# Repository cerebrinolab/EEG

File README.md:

# EEG para analise e neuro-feedback usando Arduino e circuitos DIY.

## Captura

Essa é a tela de captura, inicialmente com uma interface minimalista, com diferentes gráficos combinados para facilitar a leitura.

Primeiro gráfico - sinal x tempo:
Aqui é possível acompanhar o sinal capturado, o eixo horizontal esta graduado em mili segundos.

Segundo grafico - espectrograma:
Plota o espectro de frequancia, num intervado de 0 á 80Hz

Terceiro grafico - Grafico de barras
Semelhante ao grafico de espectro, permite visualisar de forma simples e direta, as faixas de ondas:
Delta (0 a 4 Hz)
Theta (4 a 8 Hz)
Alpha (8 a 13 Hz)
Beta (13 a 30 Hz)
Gama (30 a 80 Hz)

## Análise por Inteligência Artificial

O sinal do gráfico abaixo foi processado por I.A., treinada com datasets etiquetados para olhos abertos, fechados, piscadas e movimentos musculares.
Esse sinal com duração de 6 minutos, alternando minuto a minuto entre olhos abertos e olhos fechados, iniciando com os olhos abertos.
Atualmente a análise é feita offline, mas o objetivo é que a I.A. efetue a análise em tempo real e que a interface traduza o resultado em estímulos sonoros e visuais, possibilitando que o usuário possa aprender a controlar seus estados mentais.

## Placa
Circuito de aquisição de sinais

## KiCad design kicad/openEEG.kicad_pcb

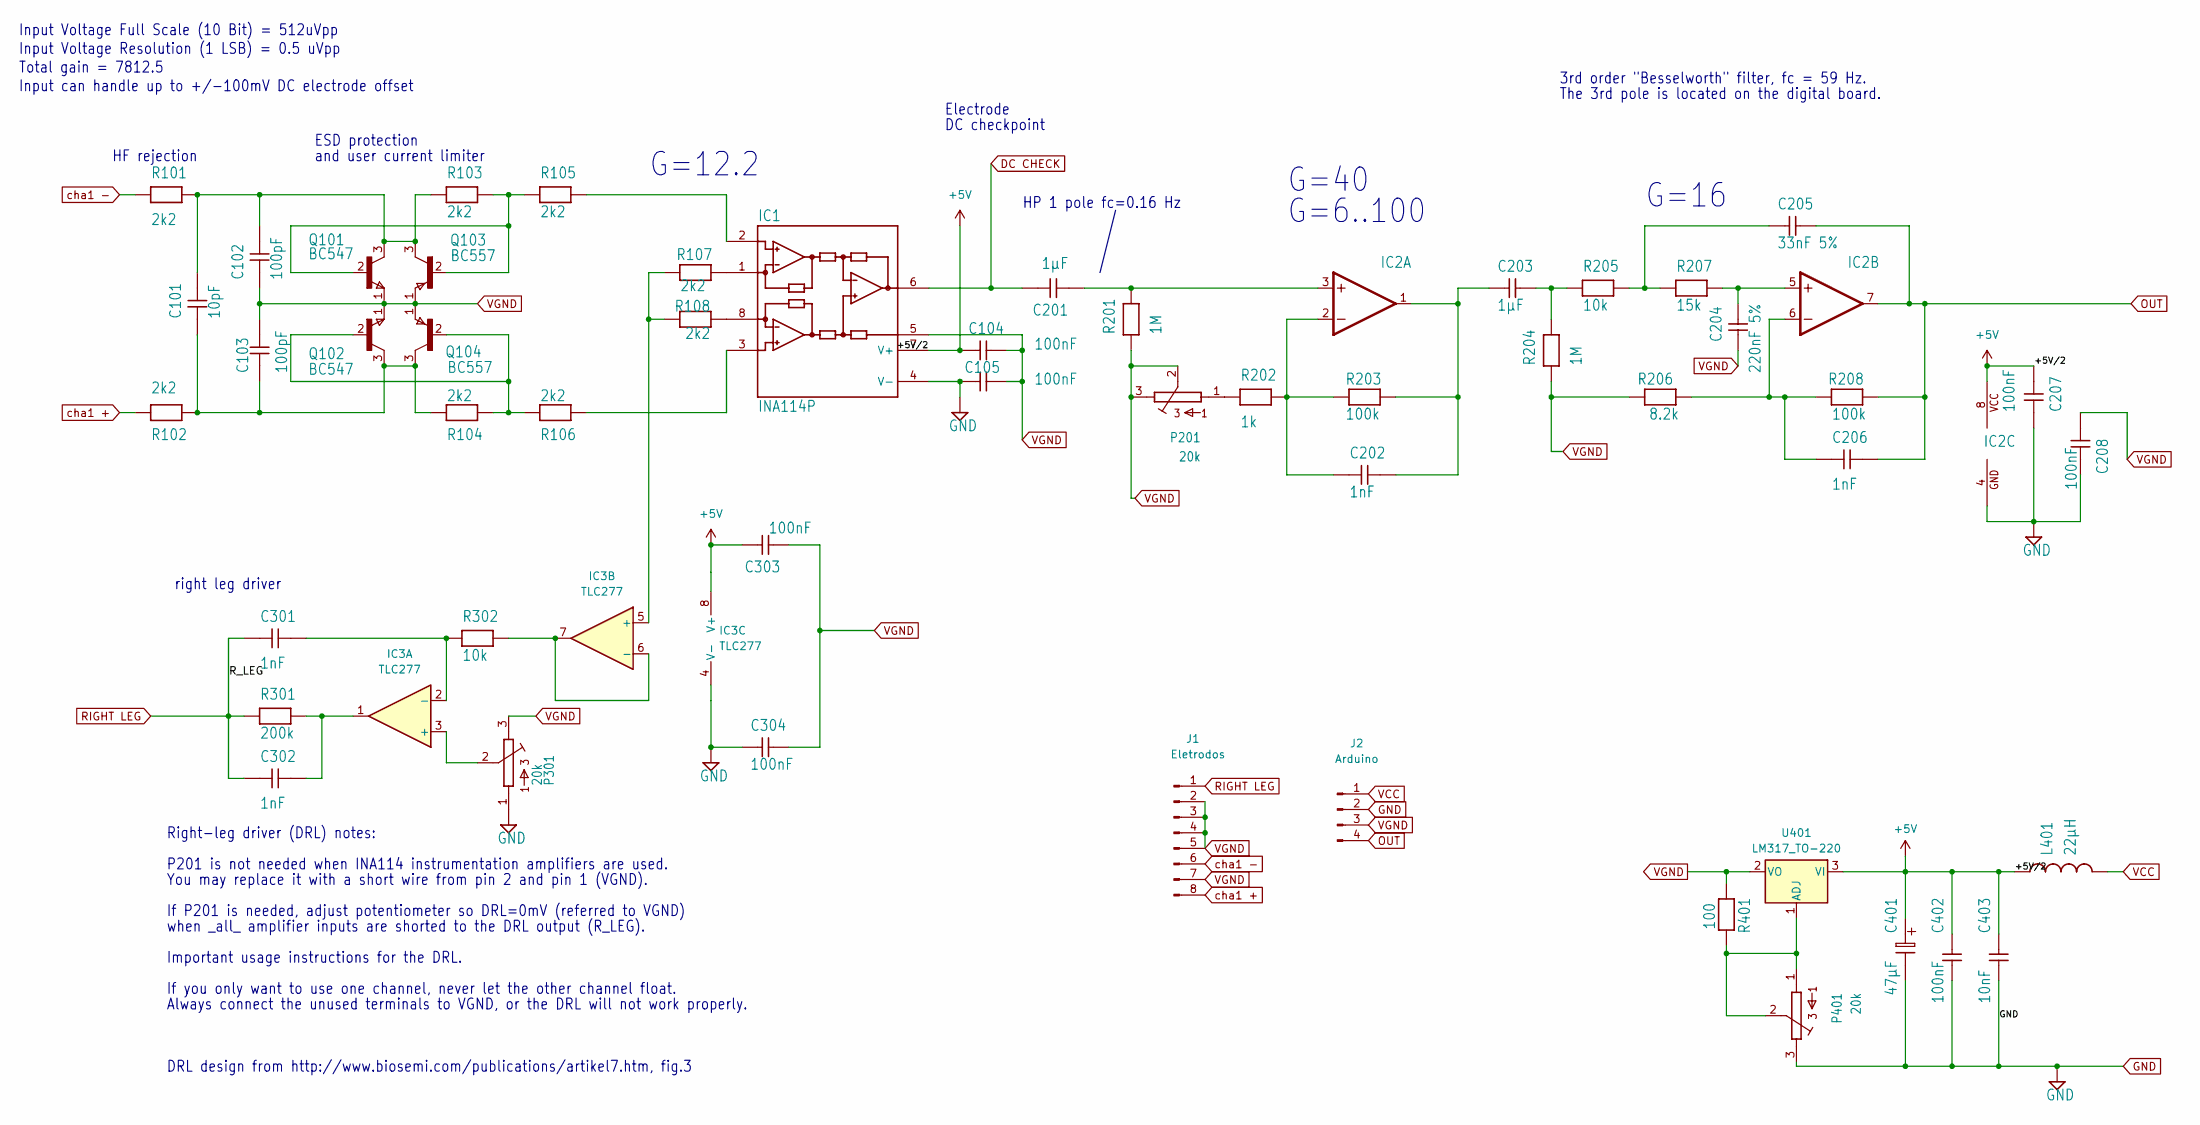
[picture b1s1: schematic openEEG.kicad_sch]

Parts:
C101: 10pF; R_Axial_DIN0204_L3.6mm_D1.6mm_P2.54mm_Vertical
C102, C103: 100pF; R_Axial_DIN0204_L3.6mm_D1.6mm_P2.54mm_Vertical
C104, C105, C207, C208, C303, C304, C402: 100nF; R_Axial_DIN0204_L3.6mm_D1.6mm_P2.54mm_Vertical
C201, C203: 1µF; CP_Radial_Tantal_D4.5mm_P2.50mm
C202, C206, C301, C302: 1nF; R_Axial_DIN0204_L3.6mm_D1.6mm_P2.54mm_Vertical
C204: 220nF 5%; R_Axial_DIN0204_L3.6mm_D1.6mm_P2.54mm_Vertical
C205: 33nF 5%; R_Axial_DIN0204_L3.6mm_D1.6mm_P2.54mm_Vertical
C401: 47µF; CP_Radial_D5.0mm_P2.50mm
C403: 10nF; R_Axial_DIN0204_L3.6mm_D1.6mm_P2.54mm_Vertical
IC1: INA114P; DIL-08
IC2: TLC277P; DIL-08
IC3: TLC277; DIL-08
J1: Eletrodos; PinHeader_2x04_P2.54mm_Vertical
J2: Arduino; PinHeader_1x04_P2.54mm_Vertical
L401: 22µH; L_Radial_L7.5mm_W4.6mm_P5.00mm_Neosid_SD75
P201, P301, P401: 20k; Potentiometer_Bourns_3386P_Vertical
Q101, Q102: BC547; TO92alinhado
Q103, Q104: BC557; TO92alinhado
R101, R102, R103, R104, R107, R108: 2k2; R_Axial_DIN0204_L3.6mm_D1.6mm_P2.54mm_Vertical
R105, R106: 2k2; R_Axial_DIN0204_L3.6mm_D1.6mm_P5.08mm_Vertical
R201, R204: 1M; R_Axial_DIN0204_L3.6mm_D1.6mm_P2.54mm_Vertical
R202: 1k; R_Axial_DIN0204_L3.6mm_D1.6mm_P2.54mm_Vertical
R203, R208: 100k; R_Axial_DIN0204_L3.6mm_D1.6mm_P2.54mm_Vertical
R205: 10k; R_Axial_DIN0204_L3.6mm_D1.6mm_P2.54mm_Vertical
R206: 8.2k; R_Axial_DIN0204_L3.6mm_D1.6mm_P2.54mm_Vertical
R207: 15k; R_Axial_DIN0204_L3.6mm_D1.6mm_P2.54mm_Vertical
R301: 200k; R_Axial_DIN0204_L3.6mm_D1.6mm_P2.54mm_Vertical
R302: 10k; R_Axial_DIN0204_L3.6mm_D1.6mm_P7.62mm_Horizontal
R401: 100; R_Axial_DIN0204_L3.6mm_D1.6mm_P2.54mm_Vertical
U401: LM317_TO-220; TO-220-3_Vertical

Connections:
+5V: C104.1, C207.2, C303.2, C401.1, C402.2, C403.2, IC1.7 (V+), IC2.8 (VCC), IC3.8 (V+), L401.1, U401.3 (VI)
DC CHECK: C201.2, IC1.6 (OUT)
GND: C105.1, C207.1, C208.1, C304.1, C401.2, C402.1, C403.1, IC1.4 (V-), IC2.4 (GND), IC3.4 (V-), J2.2, P301.1, P401.3
unnamed: C203.2, R204.2, R205.1
unnamed: C205.1, R205.2, R207.1
unnamed: C302.2, IC3.1, R301.2
unnamed: IC1.3 (+IN), R106.2
unnamed: IC1.2 (-IN), R105.2
unnamed: IC1.1 (RG), R107.1
unnamed: IC1.8 (RG@1), R108.1
unnamed: C201.1, IC2.3 (+IN), R201.2
unnamed: C202.1, IC2.2 (-IN), R202.2, R203.1
unnamed: C202.2, C203.1, IC2.1 (OUT), R203.2
unnamed: C204.2, IC2.5 (+IN), R207.2
unnamed: C206.1, IC2.6 (-IN), R206.2, R208.1
unnamed: IC3.3 (+), P301.2
unnamed: C301.2, IC3.2 (-), R302.1
unnamed: IC3.5 (+), R107.2, R108.2
unnamed: IC3.6 (-), IC3.7, R302.2
unnamed: P201.1, R202.1
unnamed: Q101.2 (B), Q103.2 (B), R103.2, R105.1
unnamed: C101.2, C102.2, Q101.3 (C), Q103.3 (C), R101.2, R103.1
unnamed: Q102.2 (B), Q104.2 (B), R104.2, R106.1
unnamed: C101.1, C103.1, Q102.3 (C), Q104.3 (C), R102.2, R104.1
unnamed: P401.1, P401.2, R401.1, U401.1 (ADJ)
OUT: C205.2, C206.2, IC2.7 (OUT), J2.4, R208.2
RIGHT LEG: C301.1, C302.1, J1.1, R301.1
VCC: J2.1, L401.2
VGND: C102.1, C103.2, C104.2, C105.2, C204.1, C208.2, C303.1, C304.2, IC1.5 (REF), J1.2, J1.3, J1.4, J1.5, J1.7, J2.3, P201.2, P201.3, P301.3, Q101.1 (E), Q102.1 (E), Q103.1 (E), Q104.1 (E), R201.1, R204.1, R206.1, R401.2, U401.2 (VO)
cha1 +: J1.8, R102.1
cha1 -: J1.6, R101.1

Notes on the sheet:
Input can handle up to +/-100mV DC electrode offset
Input Voltage Full Scale (10 Bit) = 512uVpp
If P201 is needed, adjust potentiometer so DRL=0mV (referred to VGND)
HP 1 pole fc=0.16 Hz
P201 is not needed when INA114 instrumentation amplifiers are used.
right leg driver
G=12.2
Electrode
G=16
G=6..100
DRL design from http://www.biosemi.com/publications/artikel7.htm, fig.3
when _all_ amplifier inputs are shorted to the DRL output (R_LEG).
and user current limiter
3rd order "Besselworth" filter, fc = 59 Hz.
If you only want to use one channel, never let the other channel float.
DC checkpoint
Input Voltage Resolution (1 LSB) = 0.5 uVpp
Important usage instructions for the DRL.
ESD protection
You may replace it with a short wire from pin 2 and pin 1 (VGND).
The 3rd pole is located on the digital board.
Always connect the unused terminals to VGND, or the DRL will not work properly.
G=40
Right-leg driver (DRL) notes:
HF rejection
Total gain = 7812.5

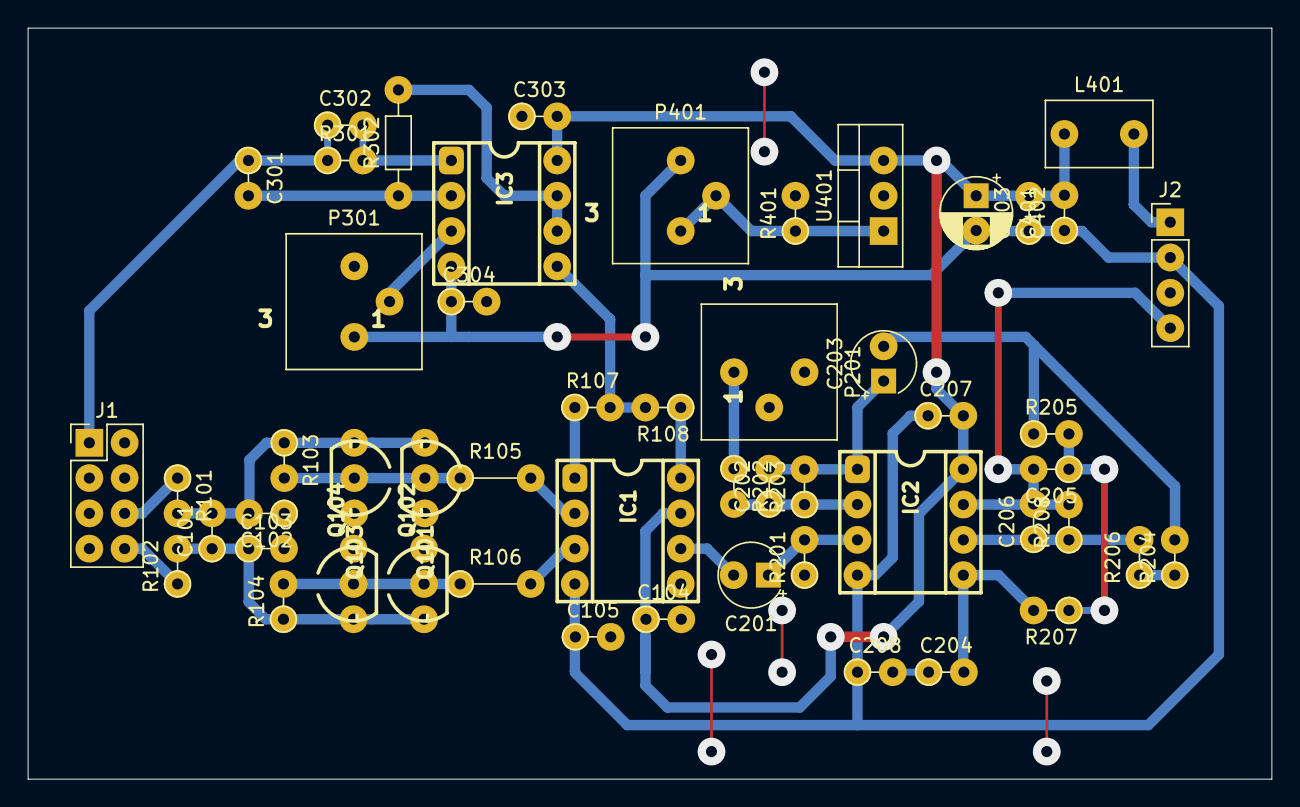
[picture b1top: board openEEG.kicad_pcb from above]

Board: 2 copper layers, 89.5 x 54.1 mm, 53 parts (0 on the bottom side), 31 nets.

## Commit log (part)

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2024-08-10 teste
2024-08-26 Atualização
2024-08-26 arquivo de exemplo
2024-09-11 publicação do circuito
2024-12-21 Create LICENSE
